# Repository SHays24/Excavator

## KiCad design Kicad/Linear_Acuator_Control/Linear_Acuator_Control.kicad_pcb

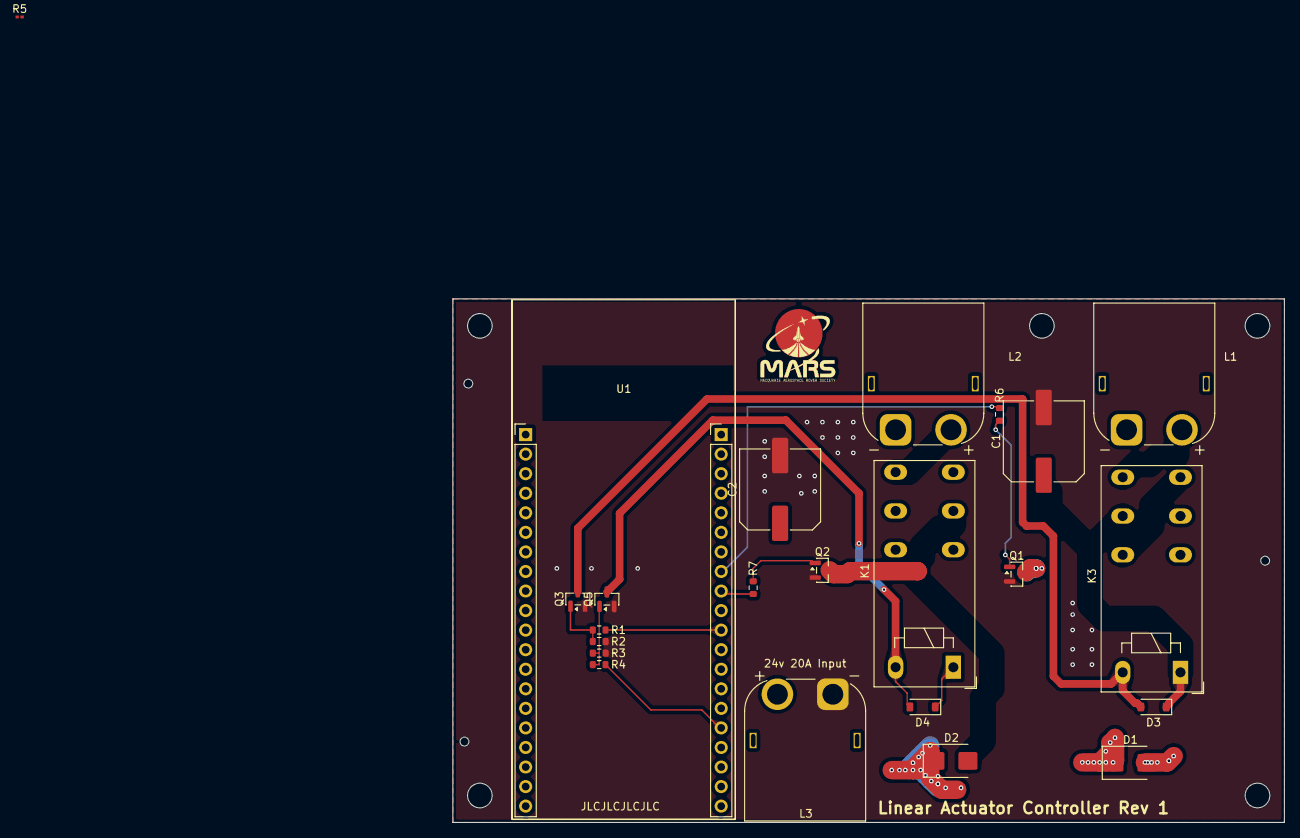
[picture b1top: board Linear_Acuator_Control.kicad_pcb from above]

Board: 2 copper layers, 108.0 x 68.0 mm, 23 parts (0 on the bottom side), 13 nets.

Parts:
C1, C2: C_Elec_10x10.2
D1, D2: MBR745; D_SMB
D3, D4: 1N4148WT; D_SOD-123
K1, K3: RT42xAxx; Relay_DPDT_Schrack-RT2-FormC_RM5mm
L1: Linear actuator 1; AMASS_XT60PW-M_1x02_P7.20mm_Horizontal
L2: Linear Actuator 2; AMASS_XT60PW-M_1x02_P7.20mm_Horizontal
L3: 24v 20A Input; AMASS_XT60PW-M_1x02_P7.20mm_Horizontal
Q1, Q2: IRLB3813; SOT-23
Q3, Q5: 2N7002; SOT-23
R1, R4: 1k; R_0603_1608Metric
R2, R3: 10k; R_0603_1608Metric
R5: 220; R_0201_0603Metric
R6, R7: 220; R_0603_1608Metric
U1: ESP32-S3-WROOM; ESP32-S3-WROOM-Cam

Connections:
+24V: D1.1 (K), D2.1 (K), D3.1 (K), D4.1 (K), K1.21, K1.A1, K3.21, K3.A1, L3.2
Dir L1: Q3.1 (G), R1.2, R2.1, U1.36 (GPIO39/MTCK)
GND: C1.2, C2.2, D1.2 (A), D2.2 (A), K1.11, K3.11, L3.1, Q1.2 (D), Q1.3 (S), Q2.2 (D), Q2.3 (S), Q3.2 (S), Q5.1 (G), Q5.2 (S), R2.2, R3.2, R4.1, R4.2
unnamed: D3.2 (A), K3.A2, Q3.3 (D)
unnamed: D4.2 (A), K1.A2, Q5.3 (D)
unnamed: K3.14, K3.22, L1.1
unnamed: K3.12, K3.24, L1.2
unnamed: K1.14, K1.22, L2.1
unnamed: K1.12, K1.24, L2.2
unnamed: Q2.1 (G), R5.2, R7.2
unnamed: U1.1 (3V3), U1.2 (3V3)
Speed L1: Q1.1 (G), R6.2, U1.39 (GPIO42/MTMS)
Speed L2: R5.1, R7.1, U1.38 (GPIO41/MTDI)

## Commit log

2026-03-28 boring line ending stuff
2026-03-29 changed to male XT60 connector
2026-03-29 Power input, minor rearranging
2026-03-29 Minor Fix
2026-03-30 changed ESP footprint name
2026-04-07 changing things to fix problems
2026-04-07 better PCB silkscreen
2026-04-09 Improving logo, solving DRCs, making renders
2026-04-09 resolve all non-pin spacing related DRCs
2026-04-09 fixing other DRC related problems
2026-04-09 smoothing capacitors
    transients hate to see me coming
2026-05-15 Commiting changes
2026-06-08 push to github, missing easyeda files atm
